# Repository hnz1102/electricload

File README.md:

<div align="center">
  <h1><code>Electric Load and Logger</code></h1>
  
</div>

# Electric Load and Logger

This is an Electric Load and Logger. It can consume the power of the device and send the data to the server.
The maximum power is 100W, maximum voltage is 30V, and maximum current is 10A. But, it must be used under 100W.
And it can measure the voltage, current, and power consumption of the device and send the data to the InfluxDB server. You can see the data on the Dashboard.

# Feature

**High Power** - It can measure the power consumption of the device up to 100W.

**Controllable** - You can control the current consumption by the device. The current can be controlled every 10mA from 10mA to 10A.

**Auto Control** - The current consumption can be controlled automatically by the device using the PID controller.

**High-resolution** - By using Texas Instruments INA228 IC - 20-bit delta-sigma ADC, It can be got measurement data with 195.uV Bus voltage and 163.84mV Shunt voltage. 

**Microcontroller on board** - No need for a client PC when you are measuring. Directly send to the server. 

**Transfer measurement data via WiFi** - This Logger can transfer data to Linux PC via WiFi network and you can see the dashboard graph in influxDB.

**Internal Memory Buffer** - If the WiFi connection is not established, the data is stored in the internal memory buffer. When the WiFi connection is established, the data is sent to the server.

# How to use the Electric Load and Logger

At first, connect the power supply to this electric load as shown in the image below. The Plus line is connected to the 'Input +' terminal, and the GND line is connected to the 'Input -' terminal. And Input- is connected to the GND terminal, and Input+ is connected to the 'VBUS' terminal. This allows the device to measure the voltage.

Then, connect the USB Power Delivery (PD) line to the USB-C port. The PD line must be connected to the USB PD Charger. This load gets power from the USB PD 12V.

After connecting the power supply, the display will show the current voltage, current, and power consumption. Then, you can set the current consumption by the device using the touch pad. Clockwise rotation increases the current, and counterclockwise rotation decreases the current. The current can be controlled every 10mA from 10mA to 10A. Fast rotation will increase or decrease the current quickly every 100mA. After setting the current, press the Center Position of the touch pad during over a second to start the load and measurement. The current consumption can be controlled automatically by the device using the PID controller.

The display shows the current, voltage, power consumption, target current, temperature, PWM duty and status of the load. 
If you start the load, the display shows the yellow color circle in the left bottom corner and blinking. If the load is stopped, the circle disappears.
After the measure, the data is sent to the server. If the WiFi connection is not established, the data is stored in the internal memory buffer. When the WiFi connection is established, the data is sent to the server. However, the memory buffer is not stored more than 4096 samples. If the some data is stored in the memory buffer, the display shows the red bar in the bottom of the display. 

You can see the realtime data using Dashboard by [InfluxDB](https://www.influxdata.com/influxdb/).

After the measure, to stop logging, press the Center Position of the touch pad during over a second. The load is stopped and the data is not sent to the server.

The dashboard shows the graphs of voltage, current, power consumption, and PWM duty. The temperature of the heat sink and FAN RPM also shown in the dashboard. 

# How to build from code and Install to the unit.

Using Ubuntu 22.04.3 LTS and ESP-IDF V5.2.1

## Prerequisites
Ensure that your system meets the following requirements before proceeding with the installation:
- Operating System: Linux-based distribution
- Required Packages: git, python3, python3-pip, gcc, build-essential, curl, pkg-config, libudev-dev, libtinfo5, clang, libclang-dev, llvm-dev, udev, libssl-dev, python3.10-venv

## Installation Steps

### 1. System Update and Package Installation
Update your system and install the necessary packages using:
```bash
sudo apt update && sudo apt -y install git python3 python3-pip gcc build-essential curl pkg-config libudev-dev libtinfo5 clang libclang-dev llvm-dev udev libssl-dev python3.10-venv
```

### 2. Rust Installation
Install Rust programming language and Cargo package manager:
```bash
curl --proto '=https' --tlsv1.2 -sSf https://sh.rustup.rs | sh
```
After installation, activate Rust by sourcing the environment:
```bash
. "$HOME/.cargo/env"
```

### 3. Additional Tools Installation
Install the following Rust tools:
- ldproxy
- espup
- cargo-espflash

Use the following commands:
```bash
cargo install ldproxy
cargo install espup
cargo install cargo-espflash
```
2024-08-12, cargo-espflash can not be compiled.
If you have an error, use the following command.
```bash
cargo install cargo-binstall
cargo binstall cargo-espflash 
```

### 4. ESP Environment Setup
Run the following command to install and update the Espressif Rust ecosystem:
```bash
espup install
espup update
```
Set up environment variables:
```bash
. ./export-esp.sh
```

### 5. Udev Rules Configuration
Configure udev rules for device permissions:
```bash
sudo sh -c 'echo "SUBSYSTEMS==\"usb\", ATTRS{idVendor}==\"303a\", ATTRS{idProduct}==\"1001\", MODE=\"0666\"" > /etc/udev/rules.d/99-esp32.rules'
sudo udevadm control --reload-rules
sudo udevadm trigger
```

### 6. Clone Repository
Clone the TimeLeapCam repository:
```bash
git clone https://github.com/hnz1102/electricload.git
cd electricload/code
```

### 7. Setting WiFi SSID, Password, etc.
Change the following configuration file: `cfg.toml`
You have to set the following parameters. WiFi SSID, Password, InfluxDB Server IP Address, InfluxDB API Key, and InfluxDB API with your ORG.
You can get the API Key from the InfluxDB Web Console. Please see the 'How to Install the influxDB and Configure the Dashboard' section No.3.

```bash
[electricload]
wifi_ssid = "<Your AP SSID>"  # Set your AP SSID
wifi_psk = "<Your AP Password>" # Set your AP Password
http_server = "<InfluxDB Server IP Address:Port>" # Set your InfluxDB Server IP Address and Port ex. 192.168.1.100:8086
pid_kp = "0.001"
pid_ki = "0.022"
pid_kd = "0.00001"
pwm_offset = "4500"
max_current_limit = "15.0"
max_power_limit = "105.0"
influxdb_api_key = "<InfluxDB API KEY>" # Set your InfluxDB API Key
influxdb_api = "/api/v2/write?org=<ORG>&bucket=LOGGER&precision=ns" # Set your InfluxDB API with your ORG and BUCKET ex. /api/v2/write?org=ORG&bucket=LOGGER&precision=ns
influxdb_tag = "currentch1"
influxdb_measurement = "electricload"
```

### 8. Build and Flash
Build the project.
```bash
cargo build --release
```

### 9. Flash the Firmware
Connect the Electric Load and Logger to your PC using a USB cable. Then, flash the firmware:
```bash
cargo espflash flash --release --monitor
```

If your device is not detected, power on the device and during the boot, press the `BOOT` button.
Then, run the flash command again.

### 10. Monitor the Output
After flashing the firmware, the console shows the booting messages.
```bash
[2024-11-24T08:43:44Z INFO ] 🚀 A new version of cargo-espflash is available: v3.2.0
[2024-11-24T08:43:44Z INFO ] Serial port: '/dev/ttyACM0'
[2024-11-24T08:43:44Z INFO ] Connecting...
[2024-11-24T08:43:44Z INFO ] Using flash stub
Finished `release` profile [optimized] target(s) in 0.19s
Chip type:         esp32s3 (revision v0.1)
Crystal frequency: 40 MHz
Flash size:        16MB
Features:          WiFi, BLE
MAC address:       xx:xx:xx:xx:xx:xx
Bootloader:        /esp32/electricload/code/target/xtensa-esp32s3-espidf/release/build/esp-idf-sys-37f4c3bc37bda4bb/out/build/bootloader/bootloader.bin
Partition table:   partitions.csv
App/part. size:    1,358,304/15,728,640 bytes, 8.64%
[2024-11-24T08:43:45Z INFO ] Segment at address '0x0' has not changed, skipping write
[2024-11-24T08:43:45Z INFO ] Segment at address '0x8000' has not changed, skipping write
[2024-11-24T08:43:46Z INFO ] Segment at address '0x10000' has not changed, skipping write
[2024-11-24T08:43:46Z INFO ] Flashing has completed!
Commands:
    CTRL+R    Reset chip
    CTRL+C    Exit

ESP-ROM:esp32s3-20210327
Build:Mar 27 2021
rst:0x15 (USB_UART_CHIP_RESET),boot:0x8 (SPI_FAST_FLASH_BOOT)
Saved PC:0x40378bb6
0x40378bb6 - rtc_isr
    at ??:??
SPIWP:0xee
mode:DIO, clock div:2
load:0x3fce3810,len:0x178c
load:0x403c9700,len:0x4
load:0x403c9704,len:0xcbc
load:0x403cc700,len:0x2d9c
entry 0x403c9914
I (27) boot: ESP-IDF v5.2.2 2nd stage bootloader
I (27) boot: compile time Nov 22 2024 19:30:56
I (27) boot: Multicore bootloader
I (30) boot: chip revision: v0.1
I (34) boot.esp32s3: Boot SPI Speed : 40MHz
I (39) boot.esp32s3: SPI Mode       : DIO
I (44) boot.esp32s3: SPI Flash Size : 16MB
I (49) boot: Enabling RNG early entropy source...
I (54) boot: Partition Table:
I (58) boot: ## Label            Usage          Type ST Offset   Length
I (65) boot:  0 nvs              WiFi data        01 02 00009000 00006000
I (72) boot:  1 phy_init         RF data          01 01 0000f000 00001000
I (80) boot:  2 factory          factory app      00 00 00010000 00f00000
I (87) boot: End of partition table
I (91) esp_image: segment 0: paddr=00010020 vaddr=3c0e0020 size=52034h (335924) map
I (183) esp_image: segment 1: paddr=0006205c vaddr=3fc9ae00 size=04ce8h ( 19688) load
I (189) esp_image: segment 2: paddr=00066d4c vaddr=40374000 size=092cch ( 37580) load
I (200) esp_image: segment 3: paddr=00070020 vaddr=42000020 size=ddea0h (908960) map
I (427) esp_image: segment 4: paddr=0014dec8 vaddr=4037d2cc size=0dae8h ( 56040) load
I (453) boot: Loaded app from partition at offset 0x10000
I (453) boot: Disabling RNG early entropy source...
I (464) cpu_start: Multicore app
I (465) octal_psram: vendor id    : 0x0d (AP)
I (465) octal_psram: dev id       : 0x02 (generation 3)
I (468) octal_psram: density      : 0x03 (64 Mbit)
I (473) octal_psram: good-die     : 0x01 (Pass)
I (478) octal_psram: Latency      : 0x01 (Fixed)
I (484) octal_psram: VCC          : 0x01 (3V)
I (489) octal_psram: SRF          : 0x01 (Fast Refresh)
I (495) octal_psram: BurstType    : 0x01 (Hybrid Wrap)
I (500) octal_psram: BurstLen     : 0x01 (32 Byte)
I (506) octal_psram: Readlatency  : 0x02 (10 cycles@Fixed)
I (512) octal_psram: DriveStrength: 0x00 (1/1)
I (518) MSPI Timing: PSRAM timing tuning index: 4
I (523) esp_psram: Found 8MB PSRAM device
I (527) esp_psram: Speed: 80MHz
I (543) cpu_start: Pro cpu start user code
I (543) cpu_start: cpu freq: 160000000 Hz
I (543) cpu_start: Application information:
I (546) cpu_start: Project name:     libespidf
I (551) cpu_start: App version:      9e8d2c8-dirty
I (557) cpu_start: Compile time:     Nov 22 2024 19:30:46
I (563) cpu_start: ELF file SHA256:  000000000...
I (568) cpu_start: ESP-IDF:          v5.2.2
I (573) cpu_start: Min chip rev:     v0.0
I (578) cpu_start: Max chip rev:     v0.99 
I (582) cpu_start: Chip rev:         v0.1
I (587) heap_init: Initializing. RAM available for dynamic allocation:
I (594) heap_init: At 3FCA4390 len 00045380 (276 KiB): RAM
I (600) heap_init: At 3FCE9710 len 00005724 (21 KiB): RAM
I (607) heap_init: At 3FCF0000 len 00008000 (32 KiB): DRAM
I (613) heap_init: At 600FE010 len 00001FD8 (7 KiB): RTCRAM
I (619) esp_psram: Adding pool of 8192K of PSRAM memory to heap allocator
I (627) spi_flash: detected chip: gd
I (631) spi_flash: flash io: dio
W (635) pcnt(legacy): legacy driver is deprecated, please migrate to `driver/pulse_cnt.h`
W (643) i2c: This driver is an old driver, please migrate your application code to adapt `driver/i2c_master.h`
W (654) timer_group: legacy driver is deprecated, please migrate to `driver/gptimer.h`
W (663) ADC: legacy driver is deprecated, please migrate to `esp_adc/adc_oneshot.h`
I (671) sleep: Configure to isolate all GPIO pins in sleep state
I (678) sleep: Enable automatic switching of GPIO sleep configuration
I (685) main_task: Started on CPU0
I (695) esp_psram: Reserving pool of 32K of internal memory for DMA/internal allocations
I (695) main_task: Calling app_main()
I (715) electricload: [Limit] Current: 15A  Power: 105W
I (715) gpio: GPIO[15]| InputEn: 0| OutputEn: 0| OpenDrain: 0| Pullup: 0| Pulldown: 0| Intr:0 
I (725) gpio: GPIO[16]| InputEn: 0| OutputEn: 0| OpenDrain: 0| Pullup: 0| Pulldown: 0| Intr:0 
I (735) electricload::displayctl: Start Display Thread.
I (735) electricload: INA228 Config: FB6A
I (735) electricload: current_lsb=3.125e-5 shunt_cal_val=2048.0 shunt_cal=2048
I (745) electricload: Max duty: 16383
I (755) electricload: Max duty: 255
I (755) gpio: GPIO[42]| InputEn: 0| OutputEn: 0| OpenDrain: 0| Pullup: 0| Pulldown: 0| Intr:0 
I (765) gpio: GPIO[41]| InputEn: 0| OutputEn: 0| OpenDrain: 0| Pullup: 0| Pulldown: 0| Intr:0 
I (775) electricload::pulscount: Start puls count thread.
I (785) pp: pp rom version: e7ae62f
I (785) net80211: net80211 rom version: e7ae62f
I (805) wifi:wifi driver task: 3fcc2b98, prio:23, stack:6656, core=0
I (805) wifi:wifi firmware version: 3e0076f
I (805) wifi:wifi certification version: v7.0
I (805) wifi:config NVS flash: disabled
I (805) wifi:config nano formating: disabled
I (815) wifi:Init data frame dynamic rx buffer num: 32
I (815) wifi:Init static rx mgmt buffer num: 10
I (825) wifi:Init management short buffer num: 32
I (825) wifi:Init static tx buffer num: 16
I (825) wifi:Init tx cache buffer num: 32
I (835) wifi:Init static tx FG buffer num: 2
I (835) wifi:Init static rx buffer size: 1600
I (845) wifi:Init static rx buffer num: 10
I (845) wifi:Init dynamic rx buffer num: 32
I (845) wifi_init: rx ba win: 6
I (965) wifi_init: tcpip mbox: 32
I (965) wifi_init: udp mbox: 6
I (965) wifi_init: tcp mbox: 6
I (965) wifi_init: tcp tx win: 5760
I (975) wifi_init: tcp rx win: 5760
I (975) wifi_init: tcp mss: 1440
I (985) wifi_init: WiFi IRAM OP enabled
I (985) wifi_init: WiFi RX IRAM OP enabled
I (995) phy_init: phy_version 670,b7bc9b9,Apr 30 2024,10:54:13
I (1035) wifi:mode : sta ()
I (1035) wifi:enable tsf
I (3985) wifi:new:<4,0>, old:<1,0>, ap:<255,255>, sta:<4,0>, prof:1
I (3985) wifi:state: init -> auth (b0)
I (3985) wifi:state: auth -> assoc (0)
I (3995) wifi:state: assoc -> run (10)
I (4005) wifi:connected with xxxxxxxx, aid = 7, channel 4, BW20, bssid = xx:xx:xx:xx:xx:xx
I (4005) wifi:security: WPA2-PSK, phy: bgn, rssi: -36
I (4005) wifi:pm start, type: 1
I (4005) wifi:dp: 1, bi: 102400, li: 3, scale listen interval from 307200 us to 307200 us
I (4015) wifi:set rx beacon pti, rx_bcn_pti: 0, bcn_timeout: 25000, mt_pti: 0, mt_time: 10000
I (4025) wifi:AP's beacon interval = 102400 us, DTIM period = 1
I (4065) electricload::wifi: Wifi connected
I (4065) esp_idf_svc::sntp: Initializing
I (4065) esp_idf_svc::sntp: Initialization complete
I (4065) electricload: NTP Sync Start..
I (7475) electricload: NTP Sync Completed: 2024-11-24 08:43:53
I (7475) electricload::transfer: Start transfer thread.
I (7475) electricload::touchpad: Start TouchPad Read Thread.
I (7485) gpio: GPIO[18]| InputEn: 0| OutputEn: 0| OpenDrain: 0| Pullup: 0| Pulldown: 0| Intr:0 
I (7495) electricload: PID Controller: KP=0.001 KI=0.022 KD=0.00001
I (7585) electricload::touchpad: TouchPad4 threshold: 1529
I (7585) electricload::touchpad: TouchPad5 threshold: 1519
I (7585) electricload::touchpad: TouchPad6 threshold: 1433
I (7585) electricload::touchpad: TouchPad7 threshold: 1523
I (7595) electricload::touchpad: TouchPad8 threshold: 297
I (7605) electricload::touchpad: TouchPad3 threshold: 1436
I (7605) electricload::touchpad: TouchPad9 threshold: 291
I (7625) electricload::touchpad: TouchPad1 threshold: 325
I (7625) electricload::touchpad: TouchPad2 threshold: 1619
I (7625) electricload::touchpad: TouchPad14 threshold: 313
I (7645) electricload::touchpad: TouchPad13 threshold: 307
I (7645) electricload::touchpad: TouchPad12 threshold: 302
I (7645) electricload::touchpad: TouchPad11 threshold: 287
I (7645) electricload::touchpad: TouchPad10 threshold: 281
I (7665) electricload::touchpad: TouchPad charge discharge times: 500 -> 1000
```

## How to Install the influxDB and Configure the Dashboard

### 1. Download [influxDB](https://docs.influxdata.com/influxdb/v2.7/install/?t=Linux) and Install.
```bash
$ wget https://dl.influxdata.com/influxdb/releases/influxdb2-2.7.0-amd64.deb
$ sudo dpkg -i influxdb2-2.7.0-amd64.deb
$ sudo service influxdb start
```

### 2. Configure the influxDB

```
Connect to the 'http://<influxDB installed PC Address>:8086'
```
Click `GET STARTED` and set `Username`, `Password`, `Initial Organization Name`, and `Initial Bucket Name`
|Term|Value|
|---|---|
|Username|Set login username as influxDB administrator web console|
|Password|Set login password as influxDB administrator web console|
|Initial Organization Name| Organization Name ex. ORG|
|Initial Bucket Name| LOGGER |

After set them, click `CONTINUE`.

### 3. Copy the operator API token.

You can see the operator API token on the browser. YOU WON'T BE ABLE TO SEE IT AGAIN!
If you want to get new API token, click `API Tokens` menu form `Sources` Icon, then click `GENERATE API TOKEN` and select `All access token`, click `Save`.
You can see a new API token and get it.
After copy the token, click `CONFIGURE LATER`.

### 4. Import the Dashboard Template.

Click the `Dashboard` icon, and select `Import Dashboard` from the `CREATE DASHBOARD` menu.

Drop the `influxdb/electric_load.json` file to `Drop a file here`, then click `IMPORT JSON AS DASHBOARD`.

You can see the `ELECTRIC LOAD` pannel on the Dashboards page.

Click this panel, and You can see the dashboard.

If you want to customize the dashboard design, click configure mark. You can change the graph design.

## Schematic, PCB Gabar Data

There is a Schematic data in hardware directory. 
If you want to make the PCB, you can order the [PCBway](https://www.pcbway.com/project/shareproject/Digitally_Controlled_Electric_Load_504eb052.html) this link.
The heat sink is not included in the schematic data. You can use the heat sink with the fan for LGA115x CPU Cooler. 

I used this [heat sink](https://www.ainex.jp/products/cc-06b/)

I guess another [heat sink](https://www.tronwire.com/collections/tronwire-cpu-coolers/products/tw-10) is also good.

This PCB is designed by [Kicad](https://www.kicad.org/). This board image photo is shown the jumper wire. But, the PCB data is already fixed the error.

UPDATE 2024-12-29: I changed the OpAmp from TSB6111ILT to OPA187IDBVR. OPA187IDBVR is a low noise and low offset voltage OpAmp. It can be used for the high precision control.

# Changelog

## v0.1.2
- **PID Control Enhancement**: Improved PID controller performance for better current regulation and stability.
- **Under Voltage Protection**: Added `under_voltage_limit` configuration parameter. When the voltage drops below this threshold, the PID controller is reset to prevent inrush current during startup or low voltage conditions.
- **Overcurrent Protection**: Implemented overcurrent protection using `max_current_limit_ratio` parameter. When the actual current exceeds the set current multiplied by this ratio, the PID controller is reset and output is set to zero to protect against excessive current flow.
- **Inrush Current Suppression**: These protection mechanisms work together to suppress inrush current during startup and abnormal conditions, ensuring safer operation.

**Note: After updating to v0.1.2, it is necessary to reconfigure the `cfg.toml` file to include the new parameters. Some PID parameters are changed, so please update them accordingly.**

## v0.1.1
- **NVS Configuration Persistence**: Added functionality to save the last load current setting to NVS (Non-Volatile Storage) and restore it on the next startup. This allows the device to remember the previous current setting even after power cycles or resets.
- **ESP-IDF Update**: Updated ESP-IDF from v5.2.1 to v5.4.2 for improved stability and latest features.
- **WiFi Reconnection Enhancement**: Added automatic WiFi reconnection functionality to maintain network connectivity during temporary disconnections.
- **Voltage Measurement Correction**: Fixed bus voltage resolution from 193.3125µV to 195.3125µV for more accurate voltage measurements.

## LICENSE
This source code is licensed under MIT. Other Hardware Schematic documents are licensed under CC-BY-SA V4.0.

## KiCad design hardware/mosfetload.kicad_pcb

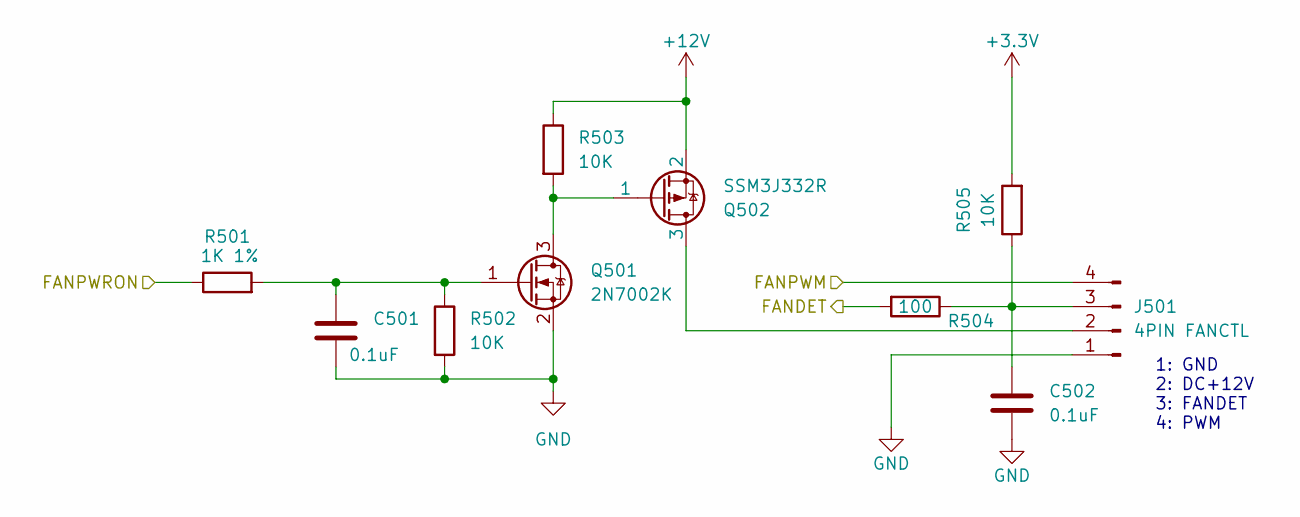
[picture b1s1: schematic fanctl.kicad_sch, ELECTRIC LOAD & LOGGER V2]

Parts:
C501, C502: 0.1uF; C_0603_1608Metric; digikey 311-1343-1-ND
J501: 4PIN FANCTL; FanPinHeader_1x04_P2.54mm_Vertical
Q501: 2N7002K; SOT-23; digikey 2N7002KCT-ND
Q502: SSM3J332R; SOT-23; digikey 4518-SSM3J332RCT-ND
R501: 1K 1%; R_0603_1608Metric; digikey 311-1.00KHRCT-ND
R502, R503, R505: 10K; R_0603_1608Metric; digikey 13-RC0603JR-1010KLCT-ND
R504: 100; R_0603_1608Metric; digikey 311-100GRCT-ND

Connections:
+3.3V: R505.2; also elsewhere on the board
+12V: Q502.2, R503.1; also elsewhere on the board
/ESP32_CONT/FANPWM: J501.4; also elsewhere on the board
/ESP32_CONT/IO41: R504.2; also elsewhere on the board
/ESP32_CONT/IO42: R501.1; also elsewhere on the board
GND: C501.2, C502.2, J501.1, Q501.2 (S), R502.2; also elsewhere on the board
unnamed: J501.2, Q502.3
unnamed: C502.1, J501.3, R504.1, R505.1
unnamed: Q501.3 (D), Q502.1, R503.2
unnamed: C501.1, Q501.1 (G), R501.2, R502.1

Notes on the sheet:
1: GND 2: DC+12V 3: FANDET 4: PWM

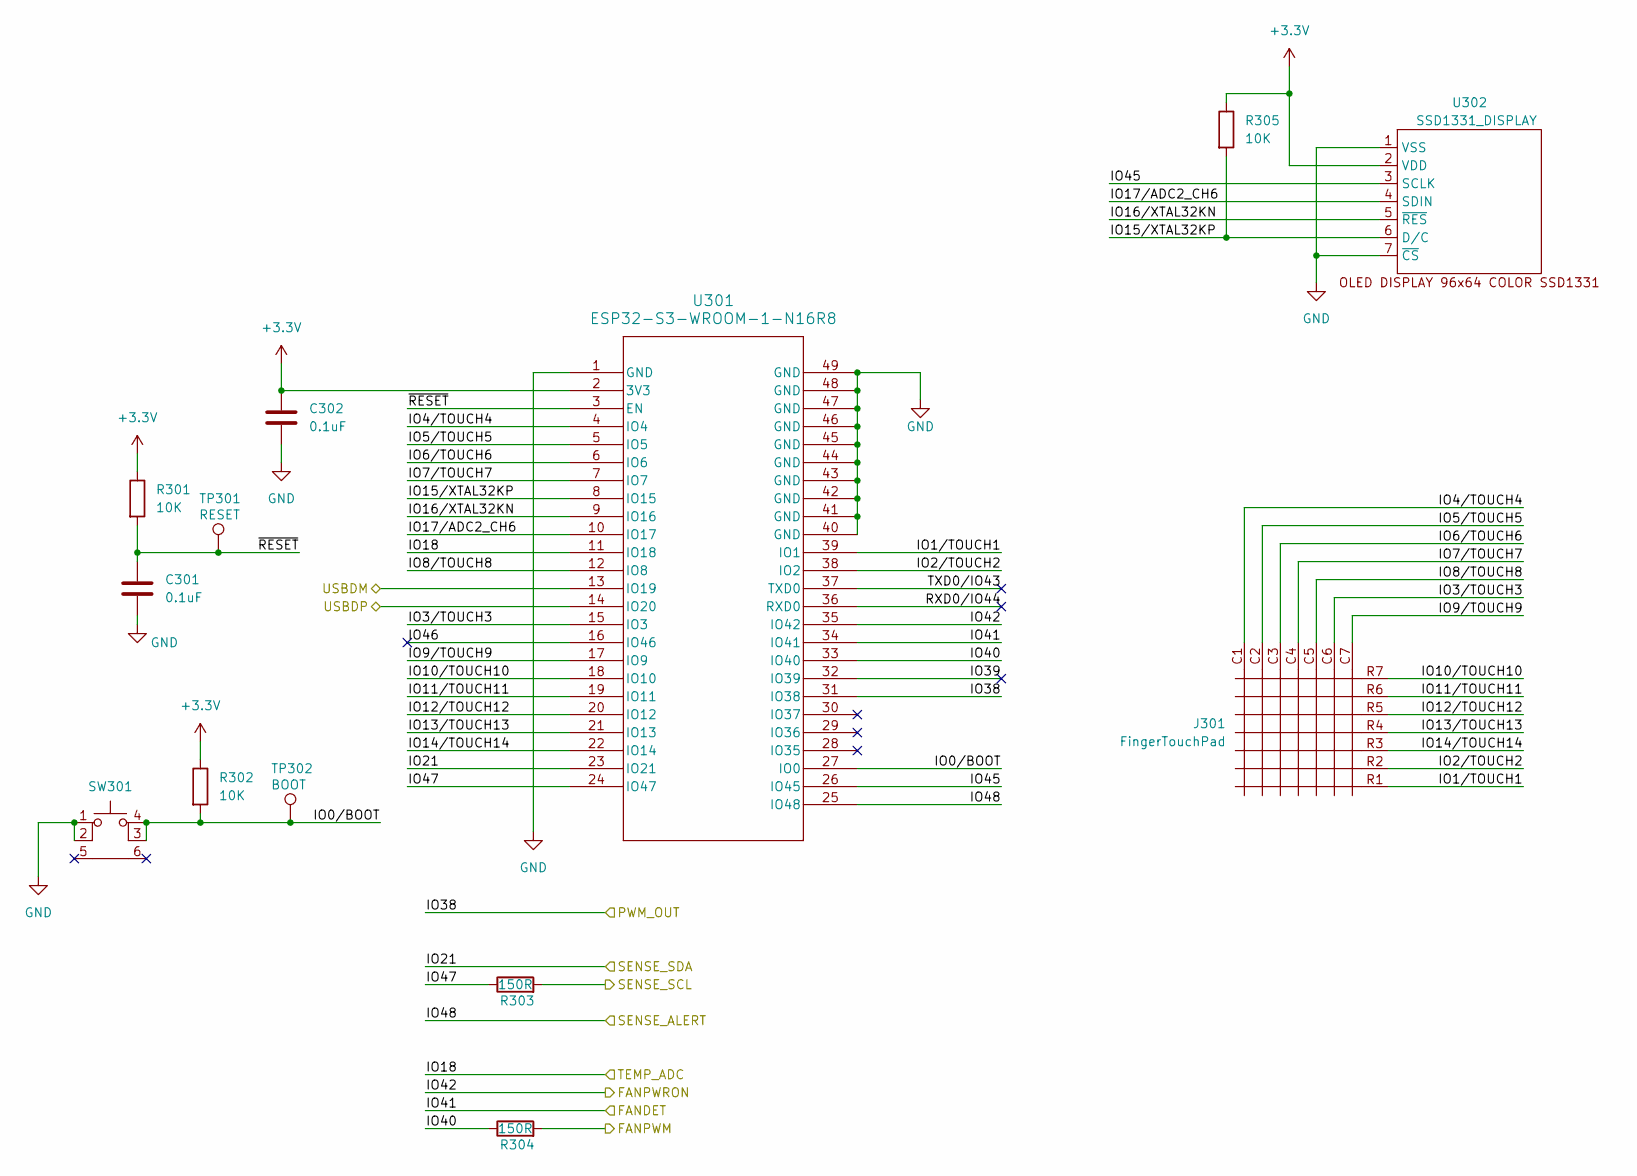
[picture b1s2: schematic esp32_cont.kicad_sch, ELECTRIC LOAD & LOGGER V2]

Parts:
C301, C302: 0.1uF; C_0603_1608Metric; digikey 311-1343-1-ND
J301: FingerTouchPad; FingerTouchPad_34x35mm
R301, R302, R305: 10K; R_0603_1608Metric; digikey 13-RC0603JR-1010KLCT-ND
R303, R304: 150R; R_0603_1608Metric; digikey 311-150GRCT-ND
SW301: 3.5x2.6 Tact SW; WS-TASV SMT Tact Switch; digikey 732-435151014824CT-ND
TP301: RESET; TestPoint_Pad_D1.0mm
TP302: BOOT; TestPoint_Pad_D1.0mm
U301: ESP32-S3-WROOM-1-N16R8; ESP32-S3-WROOM-1_EXP; digikey 1965-ESP32-S3-WROOM-1-N16R8CT-ND
U302: SSD1331_DISPLAY; OLED SSD1331 SPI DISPLAY

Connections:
+3.3V: C302.1, R301.1, R302.1, R305.1, U301.2 (3V3), U302.2 (VDD); also elsewhere on the board
/ESP32_CONT/FANPWM: R304.2; also elsewhere on the board
/ESP32_CONT/IO0/BOOT: R302.2, SW301.3 (K), SW301.4 (A), TP302.1, U301.27 (IO0)
/ESP32_CONT/IO1/TOUCH1: J301.R1, U301.39 (IO1)
/ESP32_CONT/IO2/TOUCH2: J301.R2, U301.38 (IO2)
/ESP32_CONT/IO3/TOUCH3: J301.C6, U301.15 (IO3)
/ESP32_CONT/IO4/TOUCH4: J301.C1, U301.4 (IO4)
/ESP32_CONT/IO5/TOUCH5: J301.C2, U301.5 (IO5)
/ESP32_CONT/IO6/TOUCH6: J301.C3, U301.6 (IO6)
/ESP32_CONT/IO7/TOUCH7: J301.C4, U301.7 (IO7)
/ESP32_CONT/IO8/TOUCH8: J301.C5, U301.12 (IO8)
/ESP32_CONT/IO9/TOUCH9: J301.C7, U301.17 (IO9)
/ESP32_CONT/IO10/TOUCH10: J301.R7, U301.18 (IO10)
/ESP32_CONT/IO11/TOUCH11: J301.R6, U301.19 (IO11)
/ESP32_CONT/IO12/TOUCH12: J301.R5, U301.20 (IO12)
/ESP32_CONT/IO13/TOUCH13: J301.R4, U301.21 (IO13)
/ESP32_CONT/IO14/TOUCH14: J301.R3, U301.22 (IO14)
/ESP32_CONT/IO15/XTAL32KP: R305.2, U301.8 (IO15), U302.6 (D/C)
/ESP32_CONT/IO16/XTAL32KN: U301.9 (IO16), U302.5 (~RES)
/ESP32_CONT/IO17/ADC2_CH6: U301.10 (IO17), U302.4 (SDIN)
/ESP32_CONT/IO18: U301.11 (IO18); also elsewhere on the board
/ESP32_CONT/IO21: U301.23 (IO21); also elsewhere on the board
/ESP32_CONT/IO38: U301.31 (IO38); also elsewhere on the board
/ESP32_CONT/IO39: U301.32 (IO39)
/ESP32_CONT/IO40: R304.1, U301.33 (IO40)
/ESP32_CONT/IO41: U301.34 (IO41); also elsewhere on the board
/ESP32_CONT/IO42: U301.35 (IO42); also elsewhere on the board
/ESP32_CONT/IO45: U301.26 (IO45), U302.3 (SCLK)
/ESP32_CONT/IO46: U301.16 (IO46)
/ESP32_CONT/IO47: R303.1, U301.24 (IO47)
/ESP32_CONT/IO48: U301.25 (IO48); also elsewhere on the board
/ESP32_CONT/RXD0/IO44: U301.36 (RXD0)
/ESP32_CONT/SENSE_SCL: R303.2; also elsewhere on the board
/ESP32_CONT/TXD0/IO43: U301.37 (TXD0)
/ESP32_CONT/USBDM: U301.13 (IO19); also elsewhere on the board
/ESP32_CONT/USBDP: U301.14 (IO20); also elsewhere on the board
/ESP32_CONT/~RESET: C301.1, R301.2, TP301.1, U301.3 (EN)
GND: C301.2, C302.2, SW301.1, SW301.2, U301.1 (GND), U301.40 (GND), U301.41 (GND), U301.42 (GND), U301.43 (GND), U301.44 (GND), U301.45 (GND), U301.46 (GND), U301.47 (GND), U301.48 (GND), U301.49 (GND), U302.1 (VSS), U302.7 (~CS); also elsewhere on the board

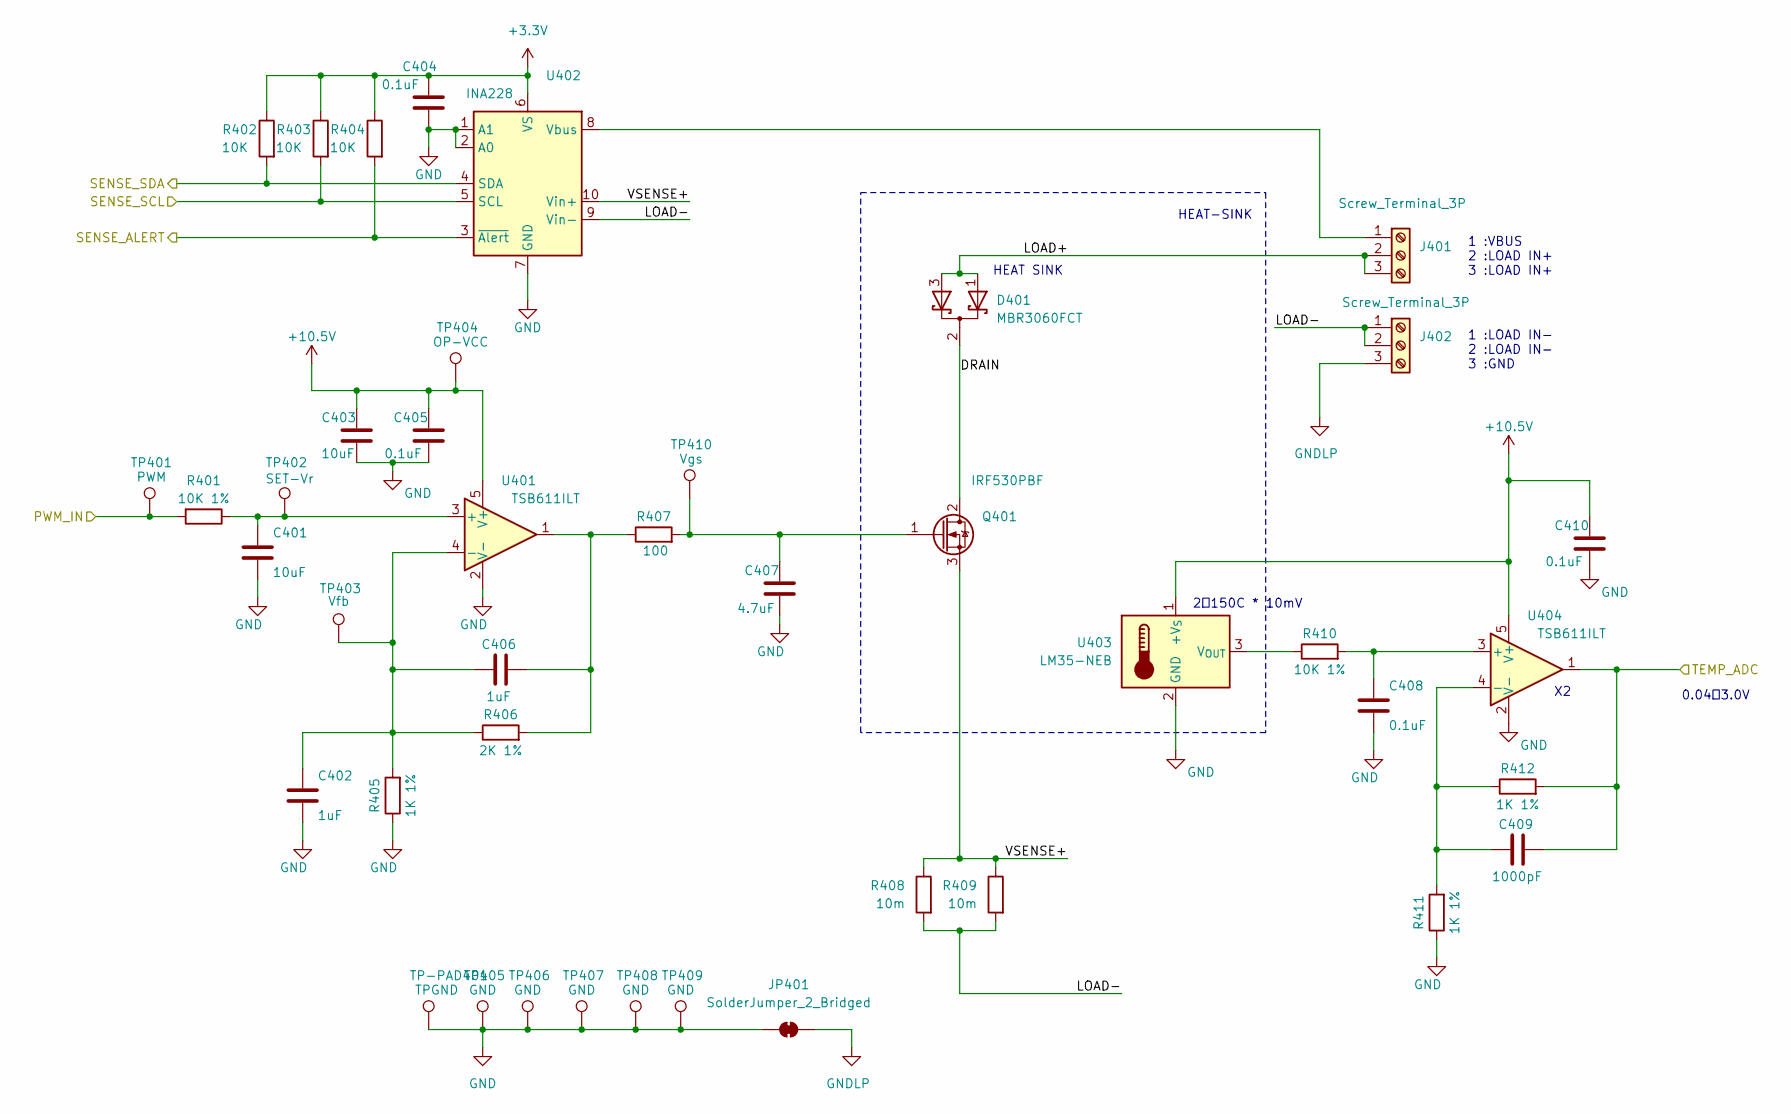
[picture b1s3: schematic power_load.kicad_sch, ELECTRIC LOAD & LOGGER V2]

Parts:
C401, C403: 10uF; C_0805_2012Metric; digikey 311-3494-1-ND
C402, C406: 1uF; C_0805_2012Metric; digikey 311-1365-1-ND
C404, C405, C408, C410: 0.1uF; C_0603_1608Metric; digikey 311-1343-1-ND
C407: 4.7uF; C_0805_2012Metric; digikey 311-1907-1-ND
C409: 1000pF; C_0603_1608Metric; digikey 311-4063-1-ND
D401: MBR3060FCT; TO-220-3_Horizontal_TabUp; digikey 3757-MBR3060FCT_T0_00001-ND
J401, J402: Screw_Terminal_3P; TB112-2-2-3-E-1 Terminal Block
JP401: SolderJumper_2_Bridged; SolderJumper-2_P1.3mm_Bridged_RoundedPad1.0x1.5mm
Q401: IRF530PBF; TO-220-3_Horizontal_TabUp; digikey IRF530PBF-ND
R401, R410: 10K 1%; R_0603_1608Metric; digikey 311-10.0KHRCT-ND
R402, R403, R404: 10K; R_0603_1608Metric; digikey 13-RC0603JR-1010KLCT-ND
R405, R411, R412: 1K 1%; R_0603_1608Metric; digikey 311-1.00KHRCT-ND
R406: 2K 1%; R_0603_1608Metric; digikey 311-2.00KHRCT-ND
R407: 100; R_0603_1608Metric; digikey 311-100GRCT-ND
R408, R409: 10m; R_10mOHM
TP401: PWM; TestPoint_Pad_D1.0mm
TP402: SET-Vr; TestPoint_Pad_D1.0mm
TP403: Vfb; TestPoint_Pad_D1.0mm
TP404: OP-VCC; TestPoint_Pad_D1.0mm
TP405, TP406, TP407, TP408, TP409: GND; TestPoint_Pad_D1.0mm
TP410: Vgs; TestPoint_Pad_D1.0mm
TP-PAD401: TPGND; TestPoint_Pad_3.2x1.6mm
U401, U404: TSB611ILT; SOT-23-5; digikey 497-16082-1-ND
U402: INA228; VSSOP-10_3x3mm_P0.5mm; digikey 296-INA228AIDGSRCT-ND
U403: LM35-NEB; TO-220-3_Horizontal_TabDown; digikey LM35DT/NOPB-ND

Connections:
+3.3V: C404.1, R402.1, R403.1, R404.1, U402.6 (VS); also elsewhere on the board
+10.5V: C403.1, C405.1, C410.1, TP404.1, U401.5 (V+), U403.1 (+V_{S}), U404.5 (V+); also elsewhere on the board
/ESP32_CONT/IO18: C409.2, R412.2, U404.1; also elsewhere on the board
/ESP32_CONT/IO21: R402.2, U402.4 (SDA); also elsewhere on the board
/ESP32_CONT/IO38: R401.2, TP401.1; also elsewhere on the board
/ESP32_CONT/IO48: R404.2, U402.3 (~Alert); also elsewhere on the board
/ESP32_CONT/SENSE_SCL: R403.2, U402.5 (SCL); also elsewhere on the board
/POWER_LOAD/DRAIN: D401.2 (K), Q401.2 (D)
/POWER_LOAD/LOAD+: D401.1 (A), D401.3 (A), J401.2, J401.3
/POWER_LOAD/LOAD-: J402.1, J402.2, R408.2, R409.2, U402.9 (Vin-)
/POWER_LOAD/VSENSE+: Q401.3 (S), R408.1, R409.1, U402.10 (Vin+)
GND: C401.2, C402.2, C403.2, C404.2, C405.2, C407.2, C408.2, C410.2, JP401.1 (A), R405.1, R411.1, TP405.1, TP406.1, TP407.1, TP408.1, TP409.1, TP-PAD401.1, U401.2 (V-), U402.1 (A1), U402.2 (A0), U402.7 (GND), U403.2 (GND), U404.2 (V-); also elsewhere on the board
GNDLP: J402.3, JP401.2 (B)
unnamed: C406.2, R406.2, R407.1, U401.1
unnamed: J401.1, U402.8 (Vbus)
unnamed: C407.1, Q401.1 (G), R407.2, TP410.1
unnamed: C401.1, R401.1, TP402.1, U401.3 (+)
unnamed: C402.1, C406.1, R405.2, R406.1, TP403.1, U401.4 (-)
unnamed: R410.1, U403.3 (V_{OUT})
unnamed: C408.1, R410.2, U404.3 (+)
unnamed: C409.1, R411.2, R412.1, U404.4 (-)

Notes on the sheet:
1 :VBUS 2 :LOAD IN+ 3 :LOAD IN+
0.04～3.0V
HEAT SINK
HEAT-SINK
1 :LOAD IN- 2 :LOAD IN- 3 :GND
2～150C * 10mV

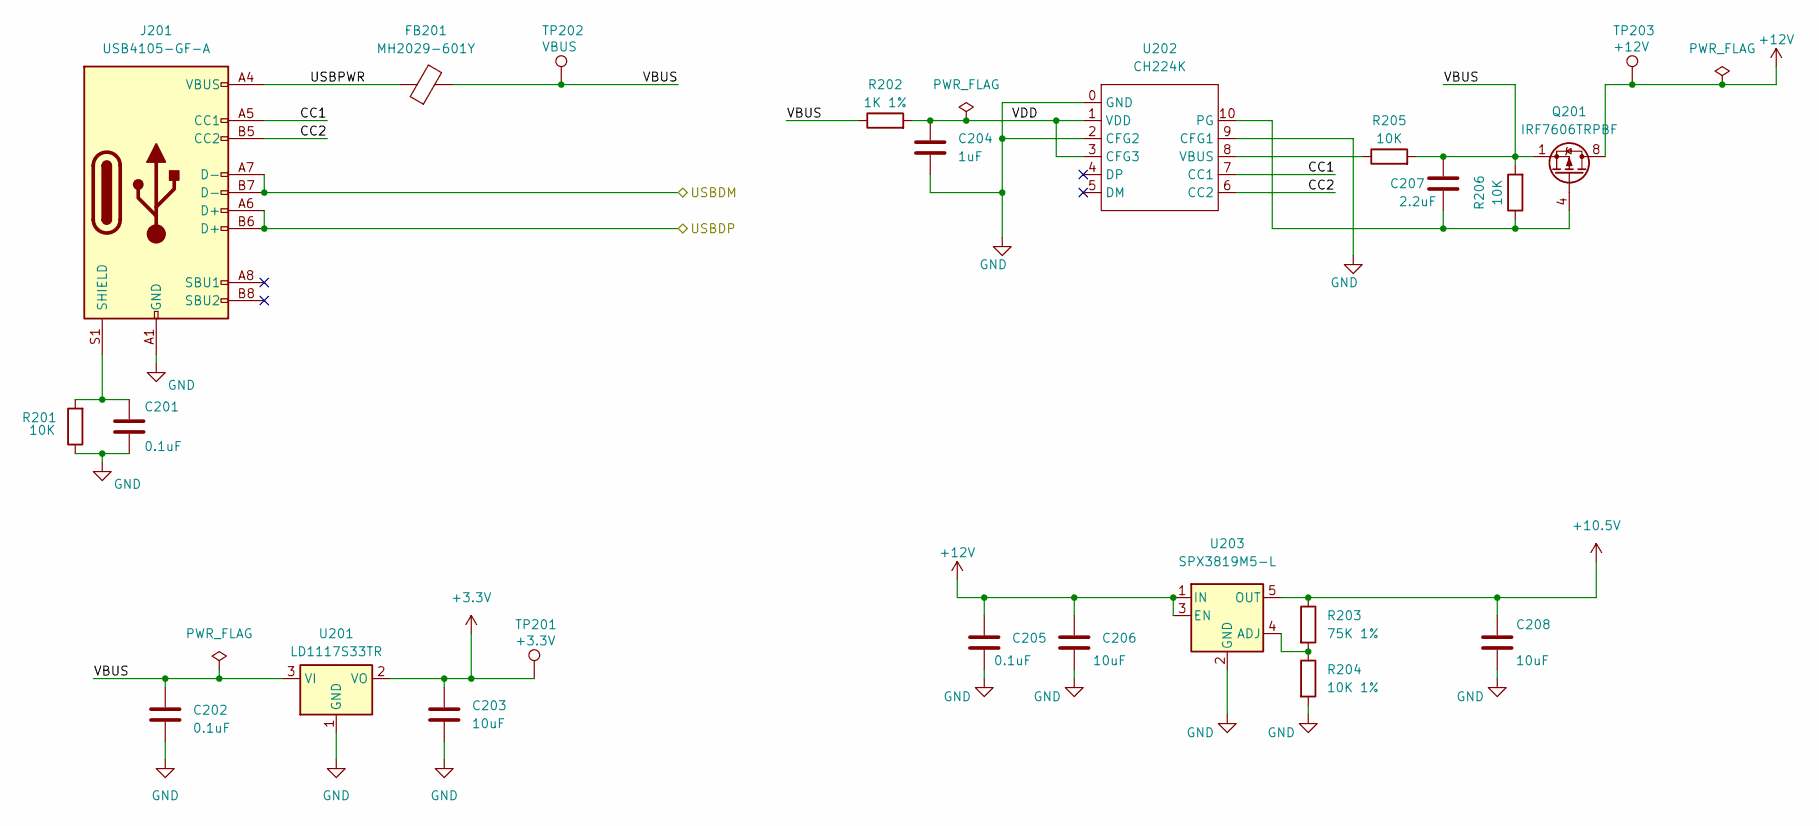
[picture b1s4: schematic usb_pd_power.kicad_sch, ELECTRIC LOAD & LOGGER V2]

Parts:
C201, C202, C205: 0.1uF; C_0603_1608Metric; digikey 311-1343-1-ND
C203, C206, C208: 10uF; C_0805_2012Metric; digikey 311-3494-1-ND
C204: 1uF; C_0805_2012Metric; digikey 311-1365-1-ND
C207: 2.2uF; C_0805_2012Metric; digikey 311-1463-1-ND
FB201: MH2029-601Y; L_0805_2012Metric; digikey MH2029-601YCT-ND
J201: USB4105-GF-A; USB_C_5077CR-16-SMC2-BK-TR; digikey 2073-USB4105-GF-ACT-ND
Q201: IRF7606TRPBF; MSOP-8_3x3mm_P0.65mm; digikey IRF7606TRPBFCT-ND
R201, R205, R206: 10K; R_0603_1608Metric; digikey 13-RC0603JR-1010KLCT-ND
R202: 1K 1%; R_0603_1608Metric; digikey 311-1.00KHRCT-ND
R203: 75K 1%; R_0603_1608Metric; digikey YAG3629CT-ND
R204: 10K 1%; R_0603_1608Metric; digikey 311-10.0KHRCT-ND
TP201: +3.3V; TestPoint_Pad_D1.0mm
TP202: VBUS; TestPoint_Pad_D1.0mm
TP203: +12V; TestPoint_Pad_D1.0mm
U201: LD1117S33TR; SOT-223-3_TabPin2; digikey 497-1242-1-ND
U202: CH224K; ESSOP-10_3.9x4.9mm_P1.00mm
U203: SPX3819M5-L; SOT-23-5; digikey 1016-1871-1-ND

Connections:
+3.3V: C203.1, TP201.1, U201.2 (VO); also elsewhere on the board
+10.5V: C208.1, R203.1, U203.5 (OUT); also elsewhere on the board
+12V: C205.1, C206.1, Q201.5 (D), Q201.6 (D), Q201.7 (D), Q201.8 (D), TP203.1, U203.1 (IN), U203.3 (EN); also elsewhere on the board
/ESP32_CONT/USBDM: J201.A7 (D-), J201.B7 (D-); also elsewhere on the board
/ESP32_CONT/USBDP: J201.A6 (D+), J201.B6 (D+); also elsewhere on the board
/USBPDPower/CC1: J201.A5 (CC1), U202.7 (CC1)
/USBPDPower/CC2: J201.B5 (CC2), U202.6 (CC2)
/USBPDPower/USBPWR: FB201.1, J201.A4 (VBUS), J201.A9 (VBUS), J201.B4 (VBUS), J201.B9 (VBUS)
/USBPDPower/VBUS: C202.1, C207.1, FB201.2, Q201.1 (S), Q201.2 (S), Q201.3 (S), R202.1, R205.2, R206.2, TP202.1, U201.3 (VI)
/USBPDPower/VDD: C204.1, R202.2, U202.1 (VDD), U202.3 (CFG3)
GND: C201.2, C202.2, C203.2, C204.2, C205.2, C206.2, C208.2, J201.A1 (GND), J201.A12 (GND), J201.B1 (GND), J201.B12 (GND), R201.1, R204.2, U201.1 (GND), U202.0 (GND), U202.2 (CFG2), U202.9 (CFG1), U203.2 (GND); also elsewhere on the board
unnamed: C201.1, J201.S1 (SHIELD), R201.2
unnamed: C207.2, Q201.4 (G), R206.1, U202.10 (PG)
unnamed: R205.1, U202.8 (VBUS)
unnamed: R203.2, R204.1, U203.4 (ADJ)

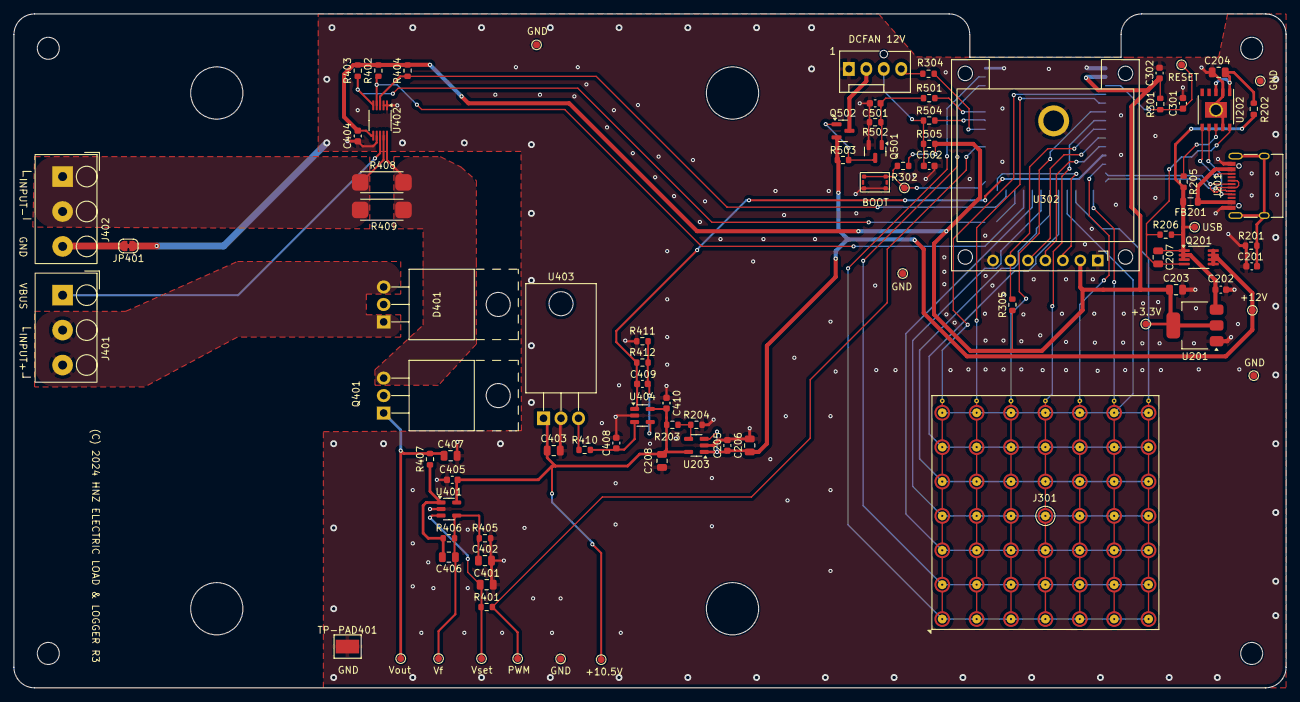
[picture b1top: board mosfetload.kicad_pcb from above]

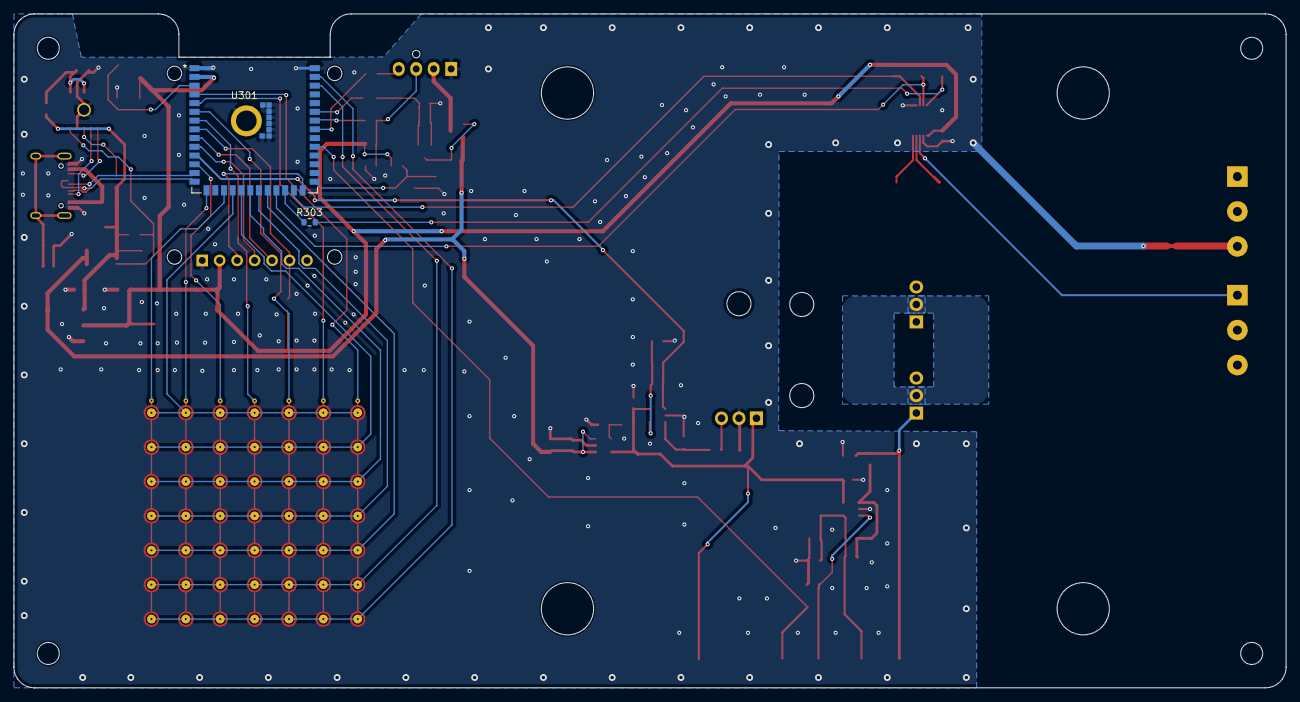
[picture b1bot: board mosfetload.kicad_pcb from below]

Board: 2 copper layers, 185.0 x 98.0 mm, 88 parts (2 on the bottom side), 62 nets.

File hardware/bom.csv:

"Reference","Value","Footprint","Qty","distributor"
"C201,C202,C205,C301,C302,C404,C405,C408,C410,C501,C502","0.1uF","Capacitor_SMD:C_0603_1608Metric","11","https://www.digikey.com/en/products/detail/yageo/CC0603ZRY5V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"
"C203,C206,C208,C401,C403","10uF","Capacitor_SMD:C_0805_2012Metric","5","https://www.digikey.com/en/products/detail/murata-electronic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"
"C204,C402,C406","1uF","Capacitor_SMD:C_0805_2012Metric","3","https://www.digikey.jp/en/products/detail/yageo/CC0805KKX7R7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"
"C207","2.2uF","Capacitor_SMD:C_0805_2012Metric","1","https://www.digikey.jp/en/products/detail/yageo/CC0805ZRY5V7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"
"C407","4.7uF","Capacitor_SMD:C_0805_2012Metric","1","https://www.digikey.jp/en/products/detail/yageo/CC0805ZKY5V7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"
"C409","1000pF","Capacitor_SMD:C_0603_1608Metric","1","https://www.digikey.jp/en/products/detail/yageo/CC0603KRX7R7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"
"D401","MBR3060FCT","Package_TO_SOT_THT:TO-220-3_Horizontal_TabUp","1","https://www.digikey.jp/en/products/detail/panjit-internation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"
"FB201","MH2029-601Y","Inductor_SMD:L_0805_2012Metric","1","https://www.digikey.com/en/products/detail/bourns-inc/MH2029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"
"J201","USB4105-GF-A","Library:USB_C_5077CR-16-SMC2-BK-TR","1","https://www.digikey.com/en/products/detail/gct/USB4105-GF-A/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"
"J301","FingerTouchPad","Library:FingerTouchPad_34x35mm","1",""
"J401,J402","Screw_Terminal_3P","Library:TB112-2-2-3-E-1 Terminal Block","2","https://akizukidenshi.com/catalog/g/g101310/"
"J501","4PIN FANCTL","Connector:FanPinHeader_1x04_P2.54mm_Vertical","1",""
"Q201","IRF7606TRPBF","Package_SO:MSOP-8_3x3mm_P0.65mm","1","https://www.digikey.jp/en/products/detail/infineon-technolog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"
"Q401","IRF530PBF","Package_TO_SOT_THT:TO-220-3_Horizontal_TabUp","1","https://www.digikey.jp/en/products/detail/vishay-siliconix/I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"
"Q501","2N7002K","Package_TO_SOT_SMD:SOT-23","1","https://www.digikey.jp/en/products/detail/onsemi/2N7002K/2060348"
"Q502","SSM3J332R","Package_TO_SOT_SMD:SOT-23","1","https://www.digikey.jp/en/products/detail/umw/SSM3J332R/24889390"
"R201,R205,R206,R301,R302,R305,R402,R403,R404,R502,R503,R505","10K","Resistor_SMD:R_0603_1608Metric","12","https://www.digikey.com/en/products/detail/yageo/RC0603JR-10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"
"R202,R405,R411,R412,R501","1K 1%","Resistor_SMD:R_0603_1608Metric","5","https://www.digikey.jp/en/products/detail/yageo/RC0603FR-071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"
"R203","75K 1%","Resistor_SMD:R_0603_1608Metric","1","https://www.digikey.jp/en/products/detail/yageo/AC0603FR-077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"
"R204,R401,R410","10K 1%","Resistor_SMD:R_0603_1608Metric","3","https://www.digikey.jp/en/products/detail/yageo/RC0603FR-071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"
"R303,R304","150R","Resistor_SMD:R_0603_1608Metric","2","https://www.digikey.jp/en/products/detail/yageo/RC0603JR-071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"
"R406","2K 1%","Resistor_SMD:R_0603_1608Metric","1","https://www.digikey.jp/en/products/detail/yageo/RC0603FR-072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"
"R407,R504","100","Resistor_SMD:R_0603_1608Metric","2","https://www.digikey.jp/en/products/detail/yageo/RC0603JR-071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"
"R408,R409","10m","Library:R_10mOHM","2","https://akizukidenshi.com/catalog/g/gP-01886/"
"SW301","3.5x2.6 Tact SW","Library:WS-TASV SMT Tact Switch","1","https://www.digikey.com/en/products/detail/w%C3%BCrth-elektr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"
"TP-PAD401","TPGND","Library:TestPoint_Pad_3.2x1.6mm","1",""
"TP201","+3.3V","TestPoint:TestPoint_Pad_D1.0mm","1",""
"TP202","VBUS","TestPoint:TestPoint_Pad_D1.0mm","1",""
"TP203","+12V","TestPoint:TestPoint_Pad_D1.0mm","1",""
"TP301","RESET","TestPoint:TestPoint_Pad_D1.0mm","1",""
"TP302","BOOT","TestPoint:TestPoint_Pad_D1.0mm","1",""
"TP401","PWM","TestPoint:TestPoint_Pad_D1.0mm","1",""
"TP402","SET-Vr","TestPoint:TestPoint_Pad_D1.0mm","1",""
"TP403","Vfb","TestPoint:TestPoint_Pad_D1.0mm","1",""
"TP404","OP-VCC","TestPoint:TestPoint_Pad_D1.0mm","1",""
"TP405,TP406,TP407,TP408,TP409","GND","TestPoint:TestPoint_Pad_D1.0mm","5",""
"TP410","Vgs","TestPoint:TestPoint_Pad_D1.0mm","1",""
"U201","LD1117S33TR","Package_TO_SOT_SMD:SOT-223-3_TabPin2","1","https://www.digikey.com/en/products/detail/stmicroelectronic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"
"U202","CH224K","Library:ESSOP-10_3.9x4.9mm_P1.00mm","1","https://akizukidenshi.com/catalog/g/g118023/"
"U203","SPX3819M5-L","Package_TO_SOT_SMD:SOT-23-5","1","https://www.digikey.com/en/products/detail/maxlinear-inc/SPX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"
"U301","ESP32-S3-WROOM-1-N16R8","Library:ESP32-S3-WROOM-1_EXP","1","https://www.digikey.com/en/products/detail/espressif-systems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"
"U302","SSD1331_DISPLAY","Library:OLED SSD1331 SPI DISPLAY","1","https://akizukidenshi.com/catalog/g/gP-14435/"
"U401,U404","TSB611ILT","Package_TO_SOT_SMD:SOT-23-5","2","https://www.digikey.jp/en/products/detail/stmicroelectronics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"
"U402","INA228","Package_SO:VSSOP-10_3x3mm_P0.5mm","1","https://www.digikey.com/en/products/detail/texas-instruments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"
"U403","LM35-NEB","Package_TO_SOT_THT:TO-220-3_Horizontal_TabDown","1","https://www.digikey.jp/en/products/detail/texas-instruments/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"

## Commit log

2024-11-24 The digit of FAN rpm is 0
2024-11-25 Add pcb documents
2024-11-25 Fixed Typo
2024-11-25 Add how to connect power source to the terminal
2024-11-26 Fixed code header
2024-12-03 Update PCB data
2024-12-04 Add PCB order info
2024-12-05 Fixed display consumed power mW
2024-12-29 Changed OpAMP part no.
2024-12-29 Fixed typo.
2024-12-29 Update BOM list

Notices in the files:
hardware/esp32_cont.kicad_sch:
(C) 2024 Hiroshi Nakajima
hardware/mosfetload.kicad_pcb:
(C) 2024 HNZ ELECTRIC LOAD & LOGGER R3
